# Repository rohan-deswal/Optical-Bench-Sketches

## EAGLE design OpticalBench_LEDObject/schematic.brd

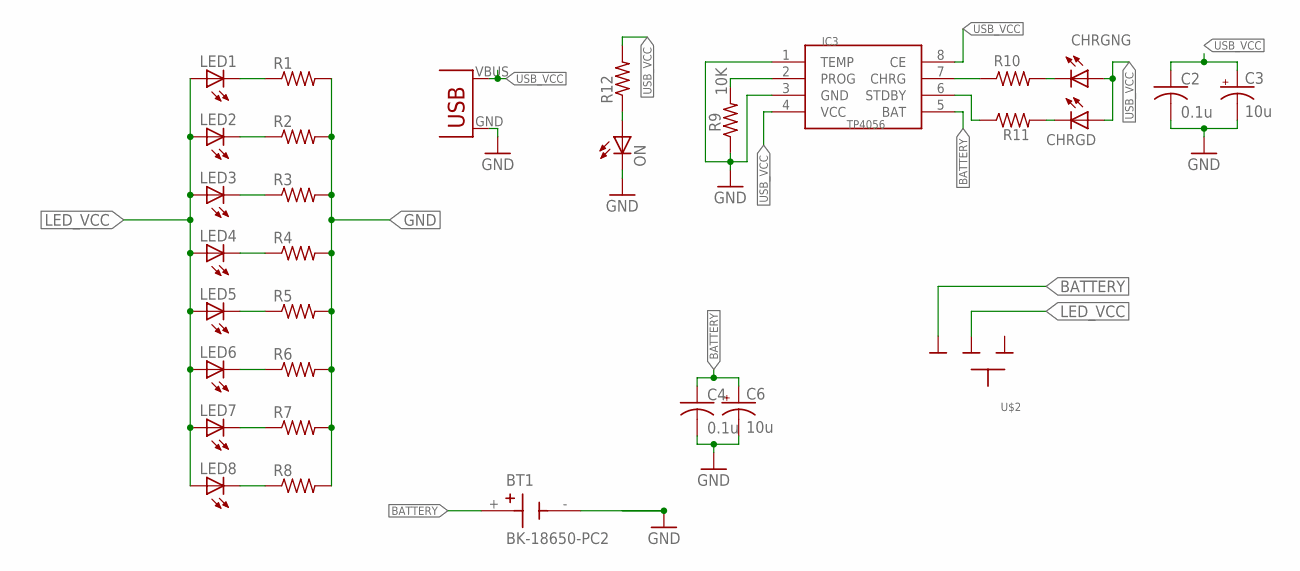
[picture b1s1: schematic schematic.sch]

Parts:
BT1: BK-18650-PC2; BAT_BK-18650-PC2
C2, C4: 0.1u; C0805
C3, C6: 10u; B/3528-21R
CHRGD: LED3MM
CHRGNG: LED3MM
IC3: TP4056; SOP-8
LED1, LED2, LED3, LED4, LED5, LED6, LED7, LED8: LED5MM
ON: LED3MM
R1, R2, R3, R4, R5, R6, R7, R8, R12: RESISTOR0207/7; 0207/7
R9: 10K; 0207/7
R10, R11: 470; 0207/7
U$1: USB(POWER)
U$2: SLIDESWITCH-SMALL; SMALLSWITCH

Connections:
BATTERY: BT1.+, C4.1, C6.+, IC3.5 (BAT), U$2.3
GND: BT1.-, C2.2, C3.-, C4.2, C6.-, IC3.1 (TEMP), IC3.3 (GND), ON.K (C), R1.2, R2.2, R3.2, R4.2, R5.2, R6.2, R7.2, R8.2, R9.1, U$1.GND
LED_VCC: LED1.A, LED2.A, LED3.A, LED4.A, LED5.A, LED6.A, LED7.A, LED8.A, U$2.2
unnamed: LED8.K (C), R8.1
unnamed: IC3.2 (PROG), R9.2
unnamed: LED7.K (C), R7.1
unnamed: LED1.K (C), R1.1
unnamed: LED2.K (C), R2.1
unnamed: IC3.7 (CHRG), R10.1
unnamed: IC3.6 (STDBY), R11.1
unnamed: CHRGNG.K (C), R10.2
unnamed: LED3.K (C), R3.1
unnamed: CHRGD.K (C), R11.2
unnamed: LED4.K (C), R4.1
unnamed: LED5.K (C), R5.1
unnamed: LED6.K (C), R6.1
unnamed: ON.A, R12.1
USB_VCC: C2.1, C3.+, CHRGD.A, CHRGNG.A, IC3.4 (VCC), IC3.8 (CE), R12.2, U$1.VBUS (VCC)

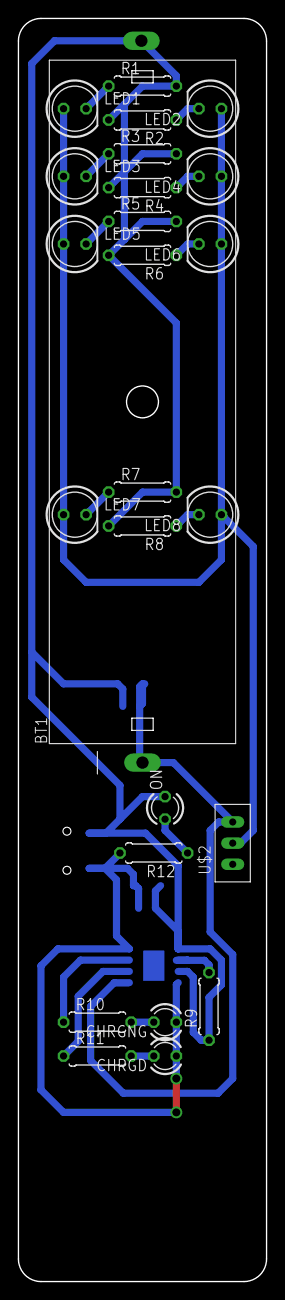
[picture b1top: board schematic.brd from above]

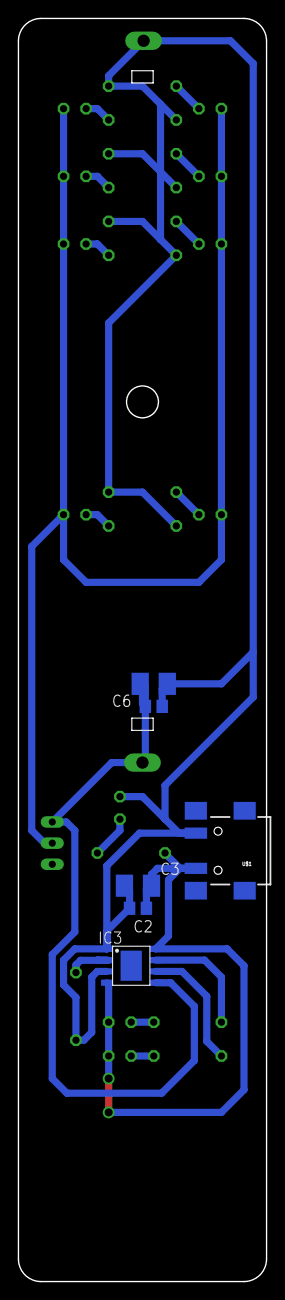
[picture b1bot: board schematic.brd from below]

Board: 2 copper layers, 27.9 x 142.2 mm, 31 parts (6 on the bottom side), 18 nets.

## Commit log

2023-01-13 LED Object Added
2023-01-13 LED Object and Files Updated
